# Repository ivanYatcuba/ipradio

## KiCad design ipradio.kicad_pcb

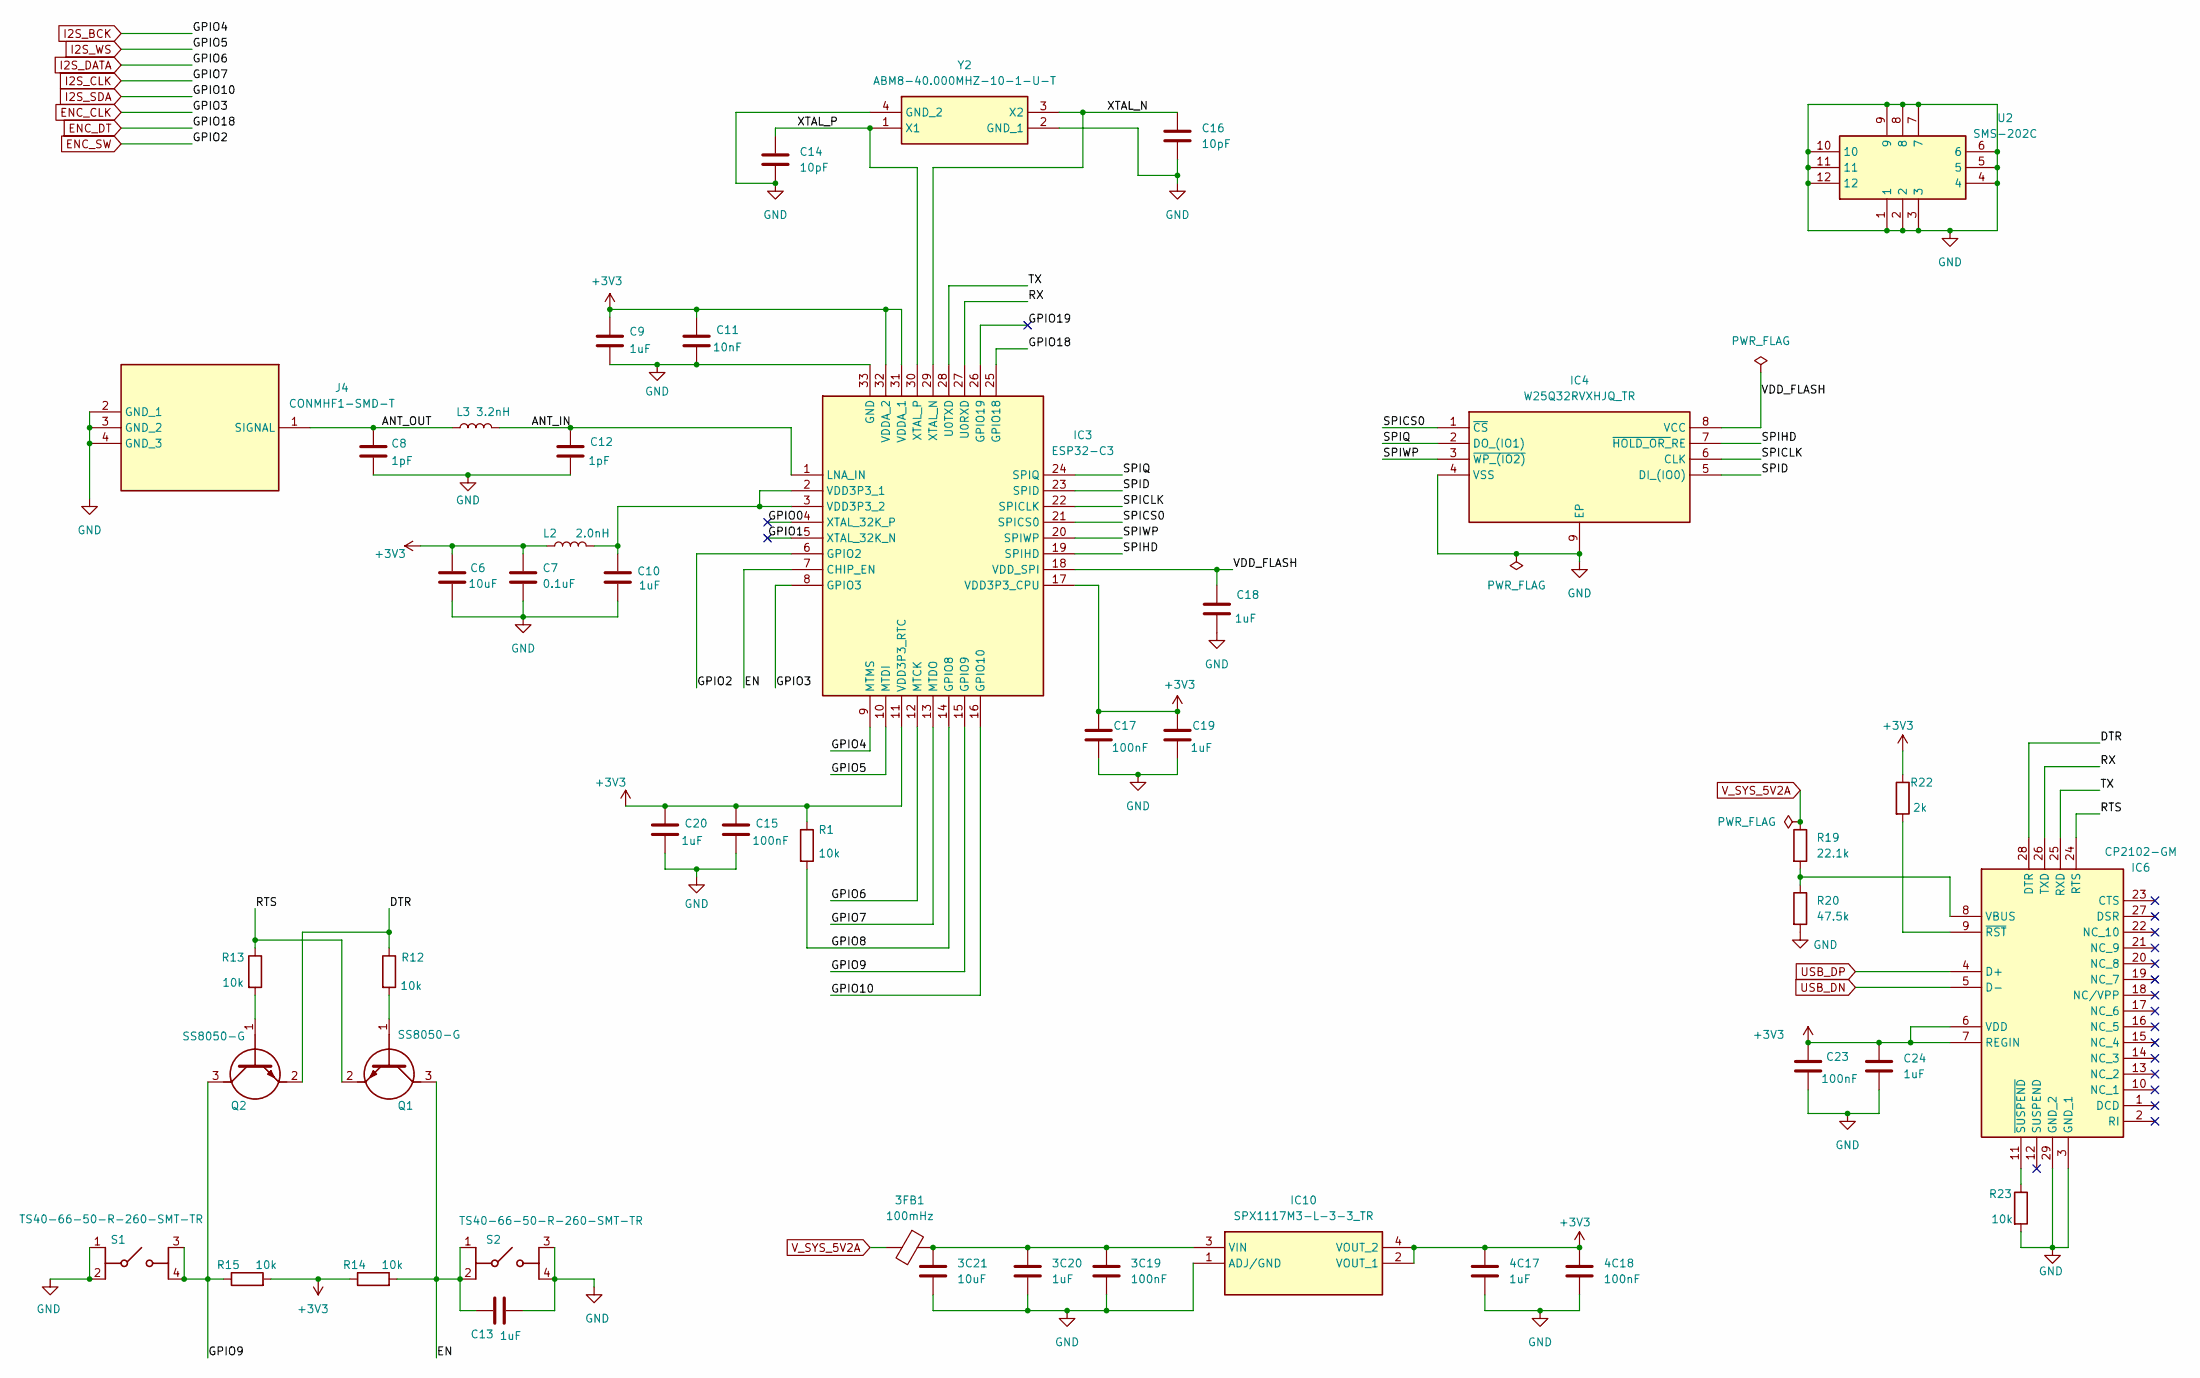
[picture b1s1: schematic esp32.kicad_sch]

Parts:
3C19, 4C18: 100nF; C_0402_1005Metric
3C20, 4C17: 1uF; C_0402_1005Metric
3C21: 10uF; C_0402_1005Metric
3FB1: 100mHz; L_0402_1005Metric
C6: 10uF; C_0805_2012Metric
C7: 0.1uF; C_0402_1005Metric
C8, C12: 1pF; C_0402_1005Metric
C9, C10, C13, C18, C19, C20, C24: 1uF; C_0402_1005Metric
C11: 10nF; C_0402_1005Metric
C14, C16: 10pF; C_0402_1005Metric
C15, C17, C23: 100nF; C_0402_1005Metric
IC3: ESP32-C3; QFN50P500X500X90-33N-D; Mouser Part Number 356-ESP32-C3
IC4: W25Q32RVXHJQ_TR; SON50P300X200X40-9N; Mouser Part Number 454-W25Q32RVXHJQTR
IC6: CP2102-GM; QFN50P500X500X100-29N-D; Mouser Part Number 634-CP2102-GM
IC10: SPX1117M3-L-3-3_TR; SOT230P700X180-4N; Mouser Part Number 701-SPX1117M3-L-33TR
J4: CONMHF1-SMD-T; CONMHF1SMDT; Mouser Part Number 712-CONMHF1-SMD-T
L2: 2.0nH; L_0402_1005Metric
L3: 3.2nH; L_0402_1005Metric
Q1, Q2: SS8050-G; SOT95P240X115-3N; Mouser Part Number 750-SS8050-G
R1, R12, R13, R14, R15, R23: 10k; R_0402_1005Metric
R19: 22.1k; R_0402_1005Metric
R20: 47.5k; R_0402_1005Metric
R22: 2k; R_0402_1005Metric
S1, S2: TS40-66-50-R-260-SMT-TR; TS406650R260SMTTR; Manufacturer_Part_Number TS40-66-50-R-260-SMT-TR
U2: SMS-202C; SMS202F; Mouser Part Number 861-SMS-202C
Y2: ABM8-40.000MHZ-10-1-U-T; ABM810000MHZ12D2W; Mouser Part Number 815-ABM8-40-10-1-U-T

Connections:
3V3: 4C17.1, 4C18.1, C6.1, C7.1, C9.1, C11.1, C15.1, C17.1, C19.1, C20.1, C23.1, C24.1, IC3.11 (VDD3P3_RTC), IC3.17 (VDD3P3_CPU), IC3.31 (VDDA_1), IC3.32 (VDDA_2), IC6.6 (VDD), IC6.7 (REGIN), IC10.2 (VOUT_1), IC10.4 (VOUT_2), L2.1, R1.1, R14.1, R15.2, R22.1; also elsewhere on the board
/esp32/ANT_IN: C12.1, IC3.1 (LNA_IN), L3.2
/esp32/ANT_OUT: C8.1, J4.1 (SIGNAL), L3.1
/esp32/DTR: IC6.28 (DTR), Q2.2 (E), R12.1
/esp32/EN: C13.1, IC3.7 (CHIP_EN), Q1.3 (C), R14.2, S2.1 (COM_1), S2.2 (COM_2)
/esp32/GPIO0: IC3.4 (XTAL_32K_P)
/esp32/GPIO1: IC3.5 (XTAL_32K_N)
/esp32/GPIO8: IC3.14 (GPIO8), R1.2
/esp32/GPIO9: IC3.15 (GPIO9), Q2.3 (C), R15.1, S1.3 (NO_1), S1.4 (NO_2)
/esp32/GPIO19: IC3.26 (GPIO19)
/esp32/RTS: IC6.24 (RTS), Q1.2 (E), R13.1
/esp32/RX: IC3.27 (U0RXD), IC6.26 (TXD)
/esp32/SPICLK: IC3.22 (SPICLK), IC4.6 (CLK)
/esp32/SPICS0: IC3.21 (SPICS0), IC4.1 (~CS)
/esp32/SPID: IC3.23 (SPID), IC4.5 (DI_(IO0))
/esp32/SPIHD: IC3.19 (SPIHD), IC4.7 (~HOLD_OR_RE)
/esp32/SPIQ: IC3.24 (SPIQ), IC4.2 (DO_(IO1))
/esp32/SPIWP: IC3.20 (SPIWP), IC4.3 (~WP_(IO2))
/esp32/TX: IC3.28 (U0TXD), IC6.25 (RXD)
/esp32/VDD_FLASH: C18.1, IC3.18 (VDD_SPI), IC4.8 (VCC)
/esp32/XTAL_N: C16.1, IC3.29 (XTAL_N), Y2.3 (X2)
/esp32/XTAL_P: C14.1, IC3.30 (XTAL_P), Y2.1 (X1)
ENC_CLK: IC3.8 (GPIO3); also elsewhere on the board
ENC_DT: IC3.25 (GPIO18); also elsewhere on the board
ENC_SW: IC3.6 (GPIO2); also elsewhere on the board
GND: 3C19.2, 3C20.2, 3C21.2, 4C17.2, 4C18.2, C6.2, C7.2, C8.2, C9.2, C10.2, C11.2, C12.2, C13.2, C14.2, C15.2, C16.2, C17.2, C18.2, C19.2, C20.2, C23.2, C24.2, IC3.33 (GND), IC4.4 (VSS), IC4.9 (EP), IC6.3 (GND_1), IC6.29 (GND_2), IC10.1 (ADJ/GND), J4.2 (GND_1), J4.3 (GND_2), J4.4 (GND_3), R20.2, R23.2, S1.1 (COM_1), S1.2 (COM_2), S2.3 (NO_1), S2.4 (NO_2), U2.1, U2.2, U2.3, U2.4, U2.5, U2.6, U2.7, U2.8, U2.9, U2.10, U2.11, U2.12, Y2.2 (GND_1), Y2.4 (GND_2); also elsewhere on the board
I2S_BCK: IC3.9 (MTMS); also elsewhere on the board
I2S_CLK: IC3.13 (MTDO); also elsewhere on the board
I2S_DATA: IC3.12 (MTCK); also elsewhere on the board
I2S_SDA: IC3.16 (GPIO10); also elsewhere on the board
I2S_WS: IC3.10 (MTDI); also elsewhere on the board
unnamed: C10.1, IC3.2 (VDD3P3_1), IC3.3 (VDD3P3_2), L2.2
unnamed: IC6.8 (VBUS), R19.2, R20.1
unnamed: IC6.9 (~RST), R22.2
unnamed: IC6.11 (~SUSPEND), R23.1
unnamed: 3C19.1, 3C20.1, 3C21.1, 3FB1.1, IC10.3 (VIN)
unnamed: Q1.1 (B), R12.2
unnamed: Q2.1 (B), R13.2
USB_DN: IC6.5 (D-); also elsewhere on the board
USB_DP: IC6.4 (D+); also elsewhere on the board
V_SYS_5V2A: 3FB1.2, R19.1; also elsewhere on the board

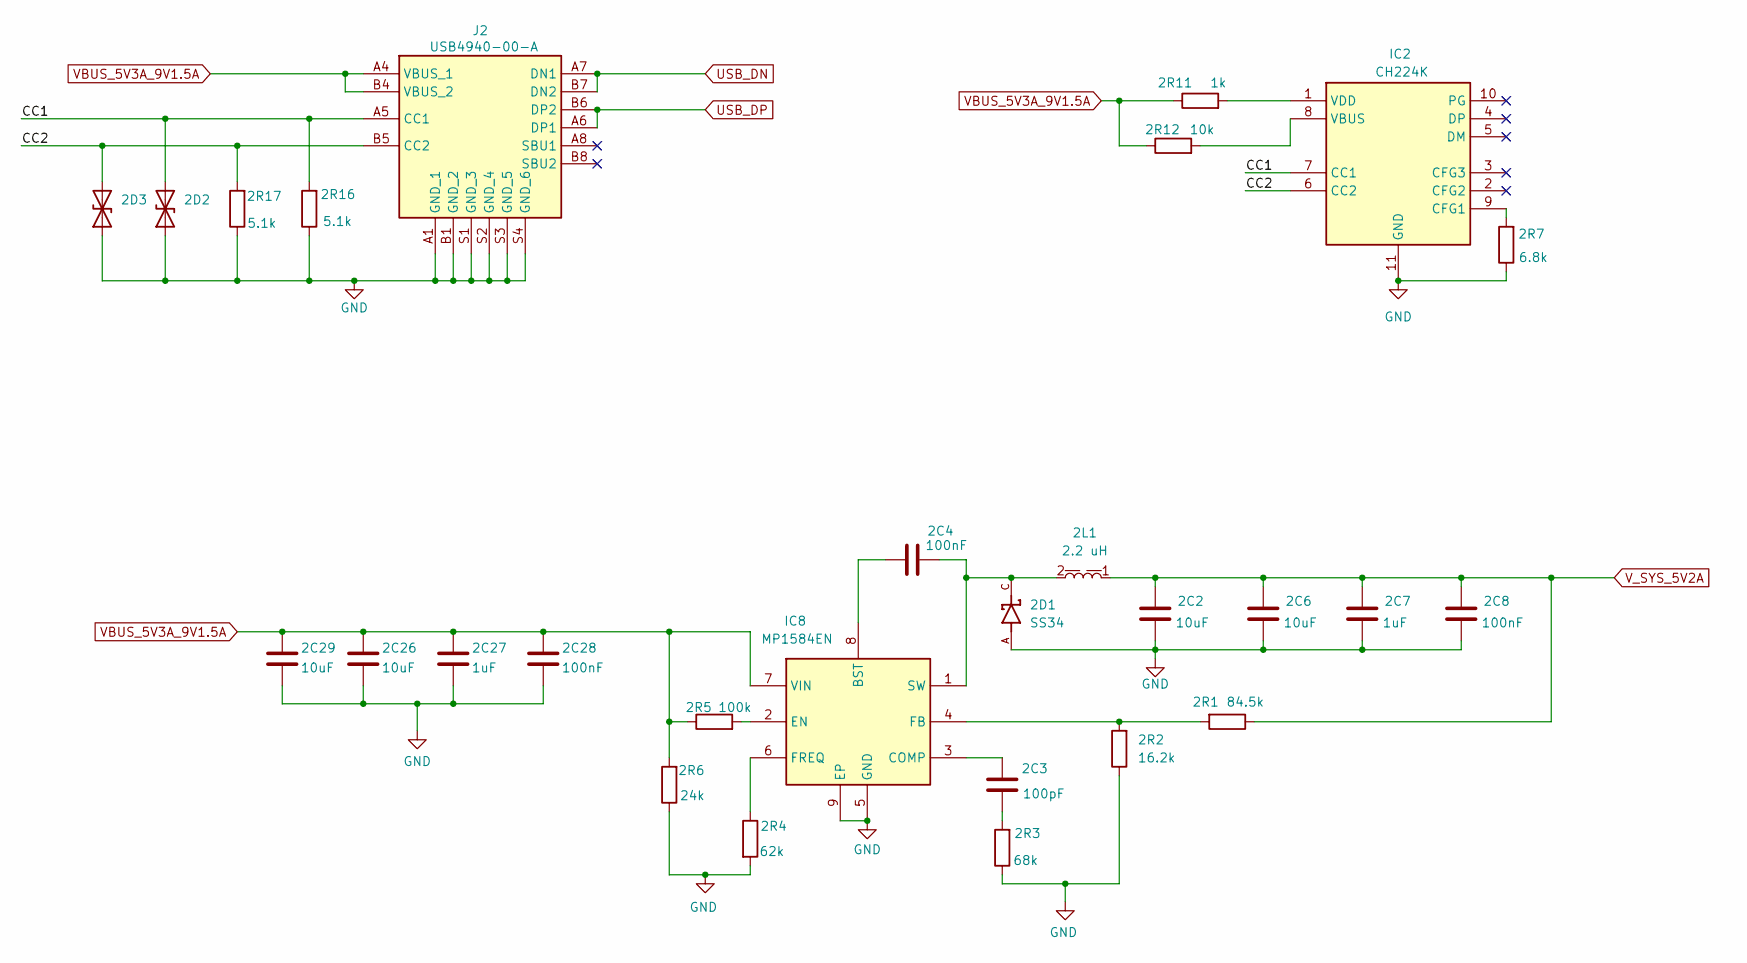
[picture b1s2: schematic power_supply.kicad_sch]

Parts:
2C2, 2C6: 10uF; C_0805_2012Metric
2C3: 100pF; C_0402_1005Metric
2C4: 100nF; C_0402_1005Metric
2C7: 1uF; C_0805_2012Metric
2C8: 100nF; C_0805_2012Metric
2C26, 2C29: 10uF; C_1206_3216Metric
2C27: 1uF; C_1206_3216Metric
2C28: 100nF; C_1206_3216Metric
2D1: SS34; DIOM7959X265N; PARTREV 31 Aug 2016
2D2, 2D3: D_TVS; D_SOD-123
2L1: 2.2 uH; L_Wurth_WE-LQS-5040; Part Number 74404054022
2R1: 84.5k; R_0402_1005Metric
2R2: 16.2k; R_0402_1005Metric
2R3: 68k; R_0402_1005Metric
2R4: 62k; R_0402_1005Metric
2R5: 100k; R_0402_1005Metric
2R6: 24k; R_0402_1005Metric
2R7: 6.8k; R_0402_1005Metric
2R11: 1k; R_0402_1005Metric
2R12: 10k; R_0402_1005Metric
2R16, 2R17: 5.1k; R_0402_1005Metric
IC2: CH224K; Manufacturer_Part_Number CH224K
IC8: MP1584EN; SOIC127P600X170-9N; Manufacturer_Part_Number MP1584EN
J2: USB4940-00-A; USB494000A; Manufacturer_Part_Number USB4940-00-A

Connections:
/power_supply/CC1: 2D2.2 (A2), 2R16.2, IC2.7 (CC1), J2.A5 (CC1)
/power_supply/CC2: 2D3.2 (A2), 2R17.2, IC2.6 (CC2), J2.B5 (CC2)
GND: 2C2.2, 2C6.2, 2C7.2, 2C8.2, 2C26.2, 2C27.2, 2C28.2, 2C29.2, 2D1.A, 2D2.1 (A1), 2D3.1 (A1), 2R2.1, 2R3.1, 2R4.2, 2R6.1, 2R7.1, 2R16.1, 2R17.1, IC2.11 (GND), IC8.5 (GND), IC8.9 (EP), J2.A1 (GND_1), J2.B1 (GND_2), J2.S1 (GND_3), J2.S2 (GND_4), J2.S3 (GND_5), J2.S4 (GND_6); also elsewhere on the board
unnamed: 2C3.1, 2R3.2
unnamed: 2R7.2, IC2.9 (CFG1)
unnamed: 2R12.2, IC2.8 (VBUS)
unnamed: 2R11.2, IC2.1 (VDD)
unnamed: 2C4.2, IC8.8 (BST)
unnamed: 2C3.2, IC8.3 (COMP)
unnamed: 2R5.2, IC8.2 (EN)
unnamed: 2R1.2, 2R2.2, IC8.4 (FB)
unnamed: 2R4.1, IC8.6 (FREQ)
unnamed: 2C4.1, 2D1.C, 2L1.2, IC8.1 (SW)
USB_DN: J2.A7 (DN1), J2.B7 (DN2); also elsewhere on the board
USB_DP: J2.A6 (DP1), J2.B6 (DP2); also elsewhere on the board
VBUS_5V3A_9V1.5A: 2C26.1, 2C27.1, 2C28.1, 2C29.1, 2R5.1, 2R6.2, 2R11.1, 2R12.1, IC8.7 (VIN), J2.A4 (VBUS_1), J2.B4 (VBUS_2)
V_SYS_5V2A: 2C2.1, 2C6.1, 2C7.1, 2C8.1, 2L1.1, 2R1.1; also elsewhere on the board

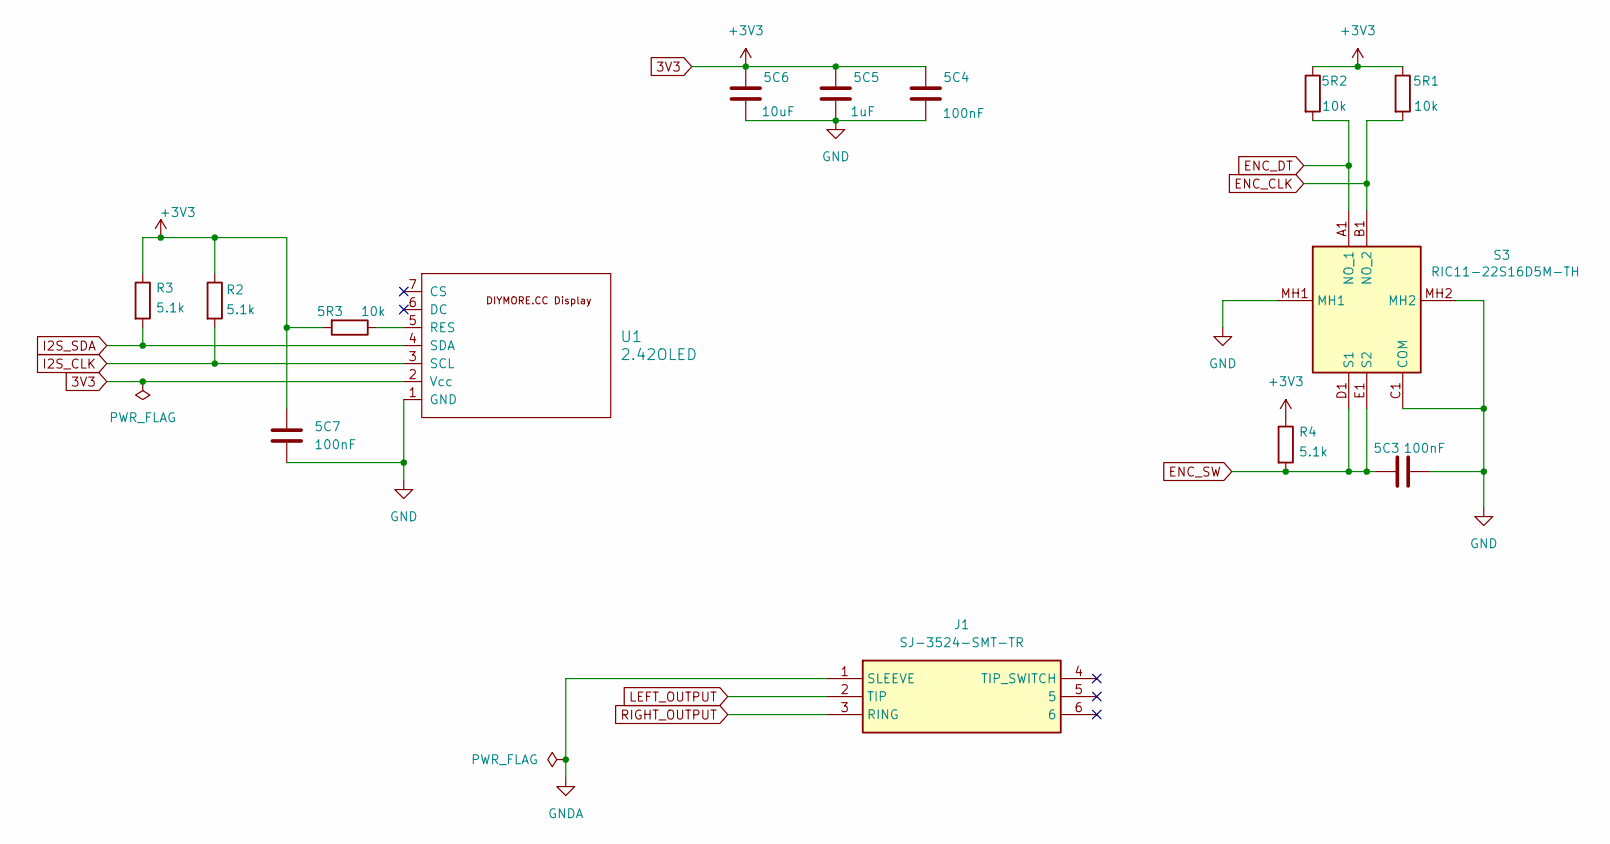
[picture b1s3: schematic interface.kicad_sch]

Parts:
5C3, 5C4, 5C7: 100nF; C_0402_1005Metric
5C5: 1uF; C_0402_1005Metric
5C6: 10uF; C_0402_1005Metric
5R1, 5R2, 5R3: 10k; R_0402_1005Metric
J1: SJ-3524-SMT-TR; SJ3524SMTTR; Manufacturer_Part_Number SJ-3524-SMT-TR; Mouser Part Number 490-SJ-3524-SMT-TR
R2, R3, R4: 5.1k; R_0402_1005Metric
S3: RIC11-22S16D5M-TH; RIC1122S16D5MTH; Mouser Part Number 179-RIC11-22S16D5MTH
U1: 2.42OLED; DIYMORE.CC

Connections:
3V3: 5C4.2, 5C5.2, 5C6.2, 5C7.1, 5R1.1, 5R2.1, 5R3.2, R2.1, R3.1, R4.1, U1.2 (Vcc); also elsewhere on the board
ENC_CLK: 5R1.2, S3.B1 (NO_2); also elsewhere on the board
ENC_DT: 5R2.2, S3.A1 (NO_1); also elsewhere on the board
ENC_SW: 5C3.1, R4.2, S3.D1 (S1), S3.E1 (S2); also elsewhere on the board
GND: 5C3.2, 5C4.1, 5C5.1, 5C6.1, 5C7.2, S3.C1 (COM), S3.MH1, S3.MH2, U1.1 (GND); also elsewhere on the board
GNDA: J1.1 (SLEEVE); also elsewhere on the board
I2S_CLK: R2.2, U1.3 (SCL); also elsewhere on the board
I2S_SDA: R3.2, U1.4 (SDA); also elsewhere on the board
LEFT_OUTPUT: J1.2 (TIP); also elsewhere on the board
unnamed: 5R3.1, U1.5 (RES)
RIGHT_OUTPUT: J1.3 (RING); also elsewhere on the board

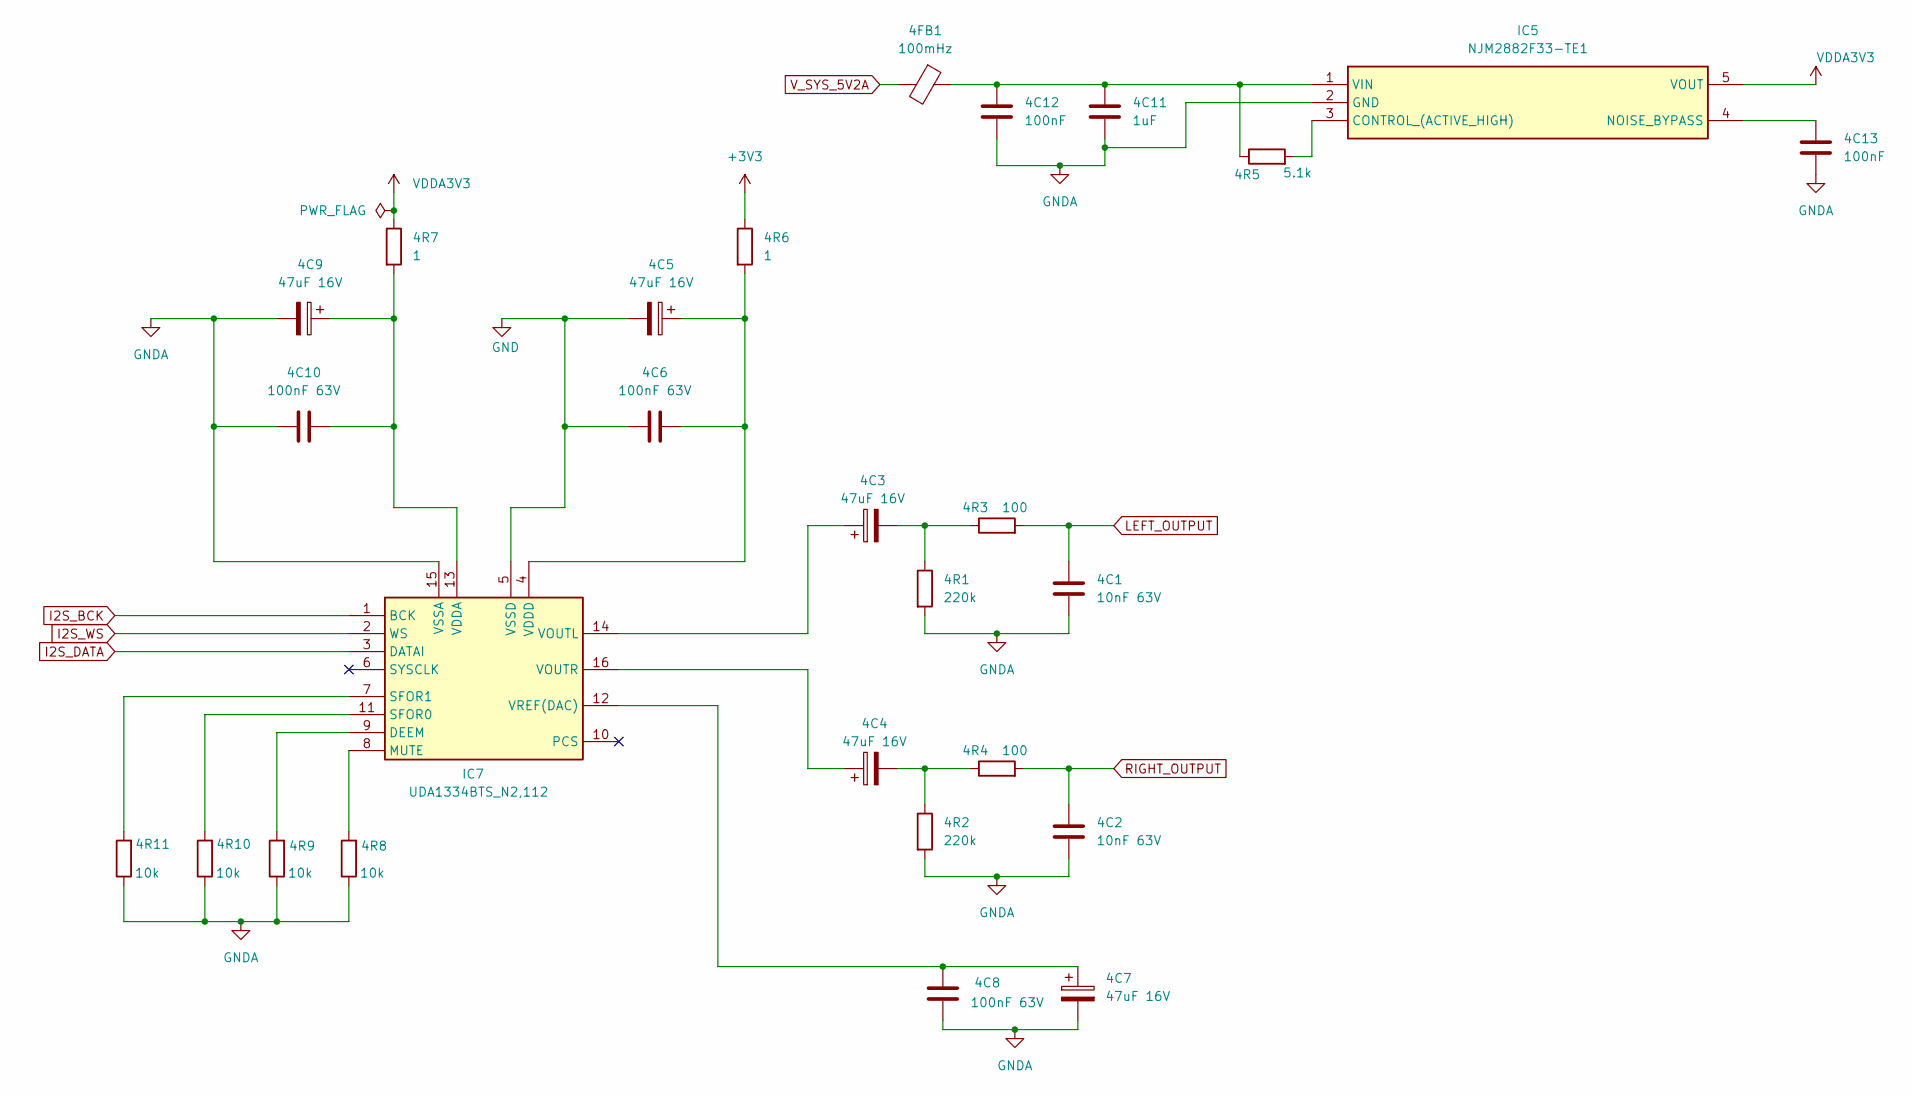
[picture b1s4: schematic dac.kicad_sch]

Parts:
4C1, 4C2: 10nF 63V; C_0402_1005Metric
4C3, 4C4, 4C5, 4C7, 4C9: 47uF 16V; CP_EIA-3528-21_Kemet-B
4C6, 4C8, 4C10: 100nF 63V; C_0402_1005Metric
4C11: 1uF; C_0402_1005Metric
4C12, 4C13: 100nF; C_0402_1005Metric
4FB1: 100mHz; L_0402_1005Metric
4R1, 4R2: 220k; R_0402_1005Metric
4R3, 4R4: 100; R_0402_1005Metric
4R5: 5.1k; R_0402_1005Metric
4R6, 4R7: 1; R_0402_1005Metric
4R8, 4R9, 4R10, 4R11: 10k; R_0402_1005Metric
IC5: NJM2882F33-TE1; SOT95P280X130-5N; Mouser Part Number 513-NJM2882F33-TE1
IC7: UDA1334BTS_N2,112; SOP65P640X150-16N; Mouser Part Number 771-UDA1334BTSDH

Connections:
3V3: 4R6.1; also elsewhere on the board
GND: 4C5.2, 4C6.2, IC7.5 (VSSD); also elsewhere on the board
GNDA: 4C1.2, 4C2.2, 4C7.2, 4C8.2, 4C9.2, 4C10.2, 4C11.2, 4C12.2, 4C13.2, 4R1.2, 4R2.2, 4R8.1, 4R9.1, 4R10.1, 4R11.1, IC5.2 (GND), IC7.15 (VSSA); also elsewhere on the board
I2S_BCK: IC7.1 (BCK); also elsewhere on the board
I2S_DATA: IC7.3 (DATAI); also elsewhere on the board
I2S_WS: IC7.2 (WS); also elsewhere on the board
LEFT_OUTPUT: 4C1.1, 4R3.2; also elsewhere on the board
unnamed: 4C3.2, 4R1.1, 4R3.1
unnamed: 4C4.2, 4R2.1, 4R4.1
unnamed: 4R5.2, IC5.3 (CONTROL_(ACTIVE_HIGH))
unnamed: 4C13.1, IC5.4 (NOISE_BYPASS)
unnamed: 4C11.1, 4C12.1, 4FB1.1, 4R5.1, IC5.1 (VIN)
unnamed: 4R9.2, IC7.9 (DEEM)
unnamed: 4R8.2, IC7.8 (MUTE)
unnamed: 4R10.2, IC7.11 (SFOR0)
unnamed: 4R11.2, IC7.7 (SFOR1)
unnamed: 4C9.1, 4C10.1, 4R7.2, IC7.13 (VDDA)
unnamed: 4C5.1, 4C6.1, 4R6.2, IC7.4 (VDDD)
unnamed: 4C3.1, IC7.14 (VOUTL)
unnamed: 4C4.1, IC7.16 (VOUTR)
unnamed: 4C7.1, 4C8.1, IC7.12 (VREF(DAC))
RIGHT_OUTPUT: 4C2.1, 4R4.2; also elsewhere on the board
VDDA3V3: 4R7.1, IC5.5 (VOUT)
V_SYS_5V2A: 4FB1.2; also elsewhere on the board

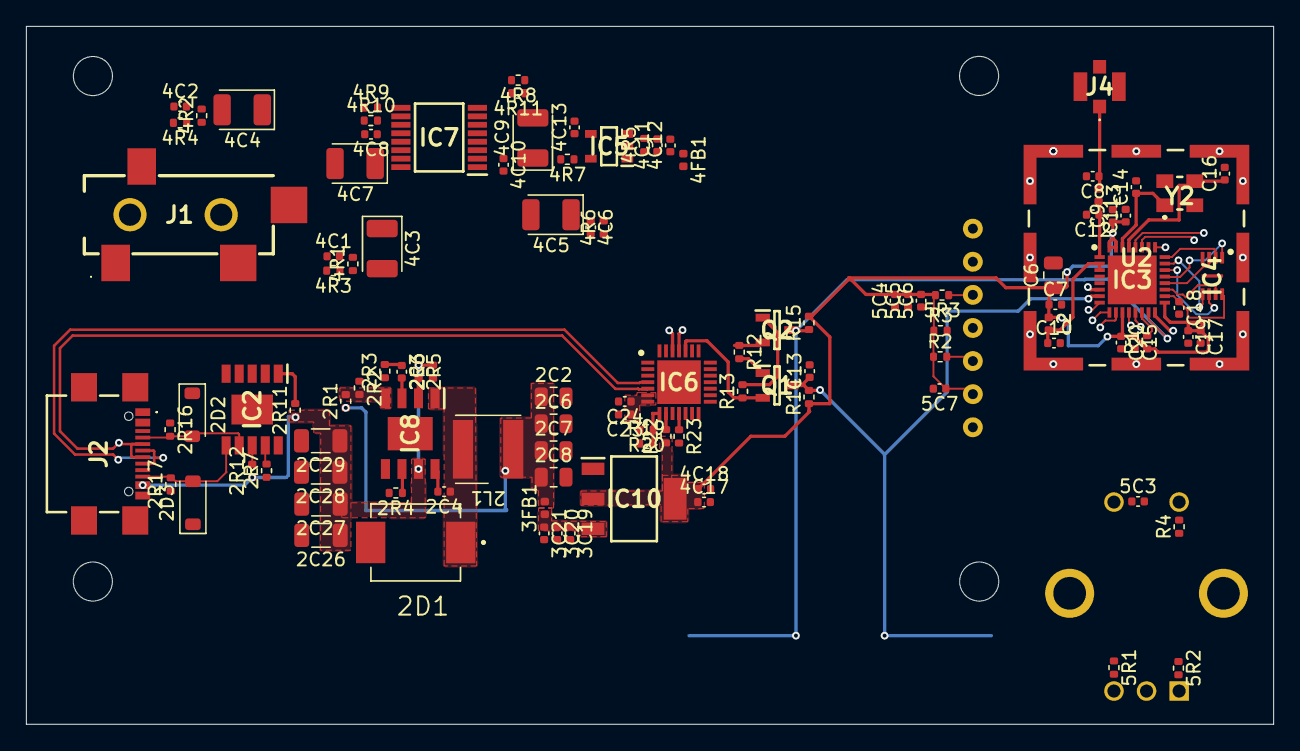
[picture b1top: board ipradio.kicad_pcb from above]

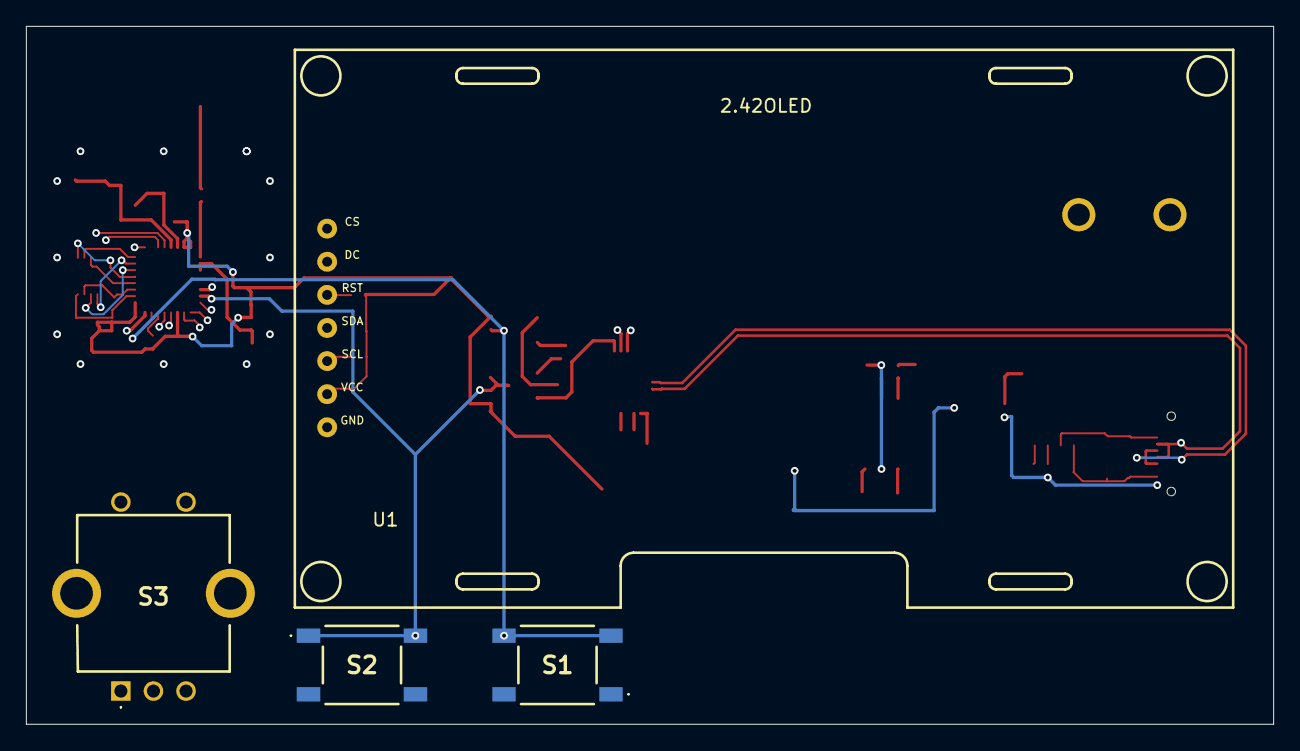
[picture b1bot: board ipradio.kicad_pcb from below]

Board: 4 copper layers, 95.7 x 53.5 mm, 114 parts (4 on the bottom side), 70 nets.

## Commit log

2026-05-31 init project and libs
2026-05-31 schematic pages add dac, oled, encoder
2026-05-31 remove backups
2026-06-02 improve power delivery schema, improve dac, added oled, encoder, audio out
2026-06-03 finalize power and esp schemas
2026-06-07 finalized schema
2026-06-07 pcb for power and esp32
